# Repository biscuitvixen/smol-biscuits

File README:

# 🍪 Smol Biscuits SlimeVR Trackers

> **Tiny, lightweight, and long-lasting SlimeVR trackers for full-body tracking**

These are a derivative of SlimeVR trackers, designed to be **smaller**, **lighter**, and **longer lasting**! Perfect for comfortable all-day body tracking.

## ✨ Features

- 🔧 **Custom PCB** - Minimal footprint carrier board
- 🏠 **Custom 3D printed case** - Flexible two-piece design
- 💾 **Custom firmware** - Optimized derivative of SlimeVR firmware
- 🔋 **Extended battery life** - Efficient power management
- 📡 **Wireless connectivity** - nRF52840-based communication

## 📋 Table of Contents

- [🔧 Hardware](#-hardware)
  - [PCB Design](#pcb-design)
  - [Sensors](#sensors)
  - [Battery](#battery)
- [🏠 3D Printed Case](#-3d-printed-case)
- [💾 Firmware](#-firmware)
- [🔨 Assembly](#-assembly)
- [📡 Setup & Calibration](#-setup--calibration)

## 🔧 Hardware

### PCB Design

The PCB is designed in **KiCad** and the files can be found in the [`pcb`](./pcb) folder. The PCB is designed to be as small as possible, acting as a carrier board for a **Seeed Studio XIAO nRF52840** on the opposite side of the sensors.

### 📊 Sensors

| Component | Model | Function |
|-----------|-------|----------|
| **IMU** | ICM-45686 | 6-axis motion sensing |
| **Magnetometer** | QMC-6309 | Magnetic field detection |

#### 🎯 IMU: ICM-45686
High-performance 6-axis motion sensor providing accurate accelerometer and gyroscope data.

#### 🧭 Magnetometer: QMC-6309
Precision 3-axis magnetic sensor for improved orientation tracking.

### 🔋 Battery

The board requires a **LiPo battery**. Size based on your needs, but the included case is designed to fit a **150mAh battery** for optimal balance between size and runtime.

## 🏠 3D Printed Case

The case features an innovative **two-piece design** with a **flexible interlink**. The battery compartment and PCB housing are separate, connected by a flexible joint that allows the tracker to bend naturally around your body.

### 🔗 Design Features

- **Flexible interlink** - Allows bending around body contours
- **Strain relief** - Protects battery cable from damage  
- **Modular design** - Separate battery and PCB compartments

### 🎨 Print Materials

| Component | Recommended Material | Reason |
|-----------|---------------------|---------|
| **Flexi-link** | TPU | Flexibility and durability |
| **Base plates** | PETG | Strength under strain |
| **Top cover** | PLA or PETG | Aesthetic preference |
| **Switch** | PLA or PETG | Aesthetic preference |

> ⚠️ **Important**: The strap piece is under significant strain - avoid PLA for base plates as it may break!

## 💾 Firmware

### 🚀 Pre-Compiled Firmware

The firmware is included as a git submodule in the [`firmware`](./firmware) folder. It's a **fork of the SlimeVR firmware** with specific support for the Smol Biscuits PCB.

📦 **Quick Start**: Use the pre-compiled firmware files from the [releases section](../../releases) to program your trackers and receiver.

### 🛠️ Compiling Firmware Yourself

Want to customize or build from source? Follow these steps:

1. **Clone with submodules**:
   ```bash
   git clone --recurse-submodules https://github.com/biscuitvixen/smol-biscuits.git
   ```

2. **Follow SlimeVR dev documentation**:
   📖 [SlimeVR Compilation Guide](https://docs.slimevr.dev/smol-slimes/firmware/smol-compiling-firmware.html)

3. **Build with correct board target**:
   ```bash
   west build -p auto -b xiao_ble -d build . -- -DNCS_TOOLCHAIN_VERSION=NONE -DBOARD_ROOT=.
   ```

## 🔨 Assembly

### 🔧 Soldering the PCB

> ⚠️ **Safety First**: Use proper ventilation and ESD protection when soldering

#### Step-by-step Process:

1. **Solder sensor components** 📊
   - Solder the sensor components onto the PCB
   - ⚠️ Leave the XIAO nRF52840 for later

2. **Prepare battery terminals** 🔋
   - Pre-tin the battery terminals on the XIAO
   - Pre-tin the corresponding footprint on the PCB

3. **Position the XIAO** 📱
   - Use the solder jig to place the XIAO nRF52840
   - **Battery terminals facing up** ⬆️

4. **Apply flux and align** ✨
   - Apply flux to all connections
   - Place sensor PCB on top, aligning battery terminals

5. **Heat and bond** 🔥
   - Use square heat pass-through pads to melt solder
   - Apply gentle pressure to flatten boards together
   - Allow to cool completely ❄️

6. **Inspect and test** 🔍
   - Visual inspection of all joints
   - **Use multimeter to check for shorts** ⚡

7. **Complete connections** 🔗
   - Solder all castellated pins around PCB edge
   - Solder battery to back of sensor board

### 💾 Programming the PCB

#### Tracker Programming:

1. **Connect** 🔌 - USB-C cable to computer
2. **Bootloader mode** 🔄 - Double-tap reset button  
3. **Flash bootloader** 📥 - Copy `update-slimenrf_xiao_sense_bootloader-0.9.2-SlimeVR.7_nosd.uf2`
4. **Verify** ✅ - Should show as `SLIMENRF_XIAO_SENSE` drive
5. **Flash firmware** 🎯 - Copy `firmware_tracker.uf2` to drive
6. **Reboot** 🔄 - Device will restart with new firmware

#### 📡 Programming the Receiver

**For Holyiot receiver**:
- Use Nordic nRF Connect Programmer
- Flash `firmware_receiver.hex` file
- Follow [SlimeVR receiver documentation](https://docs.slimevr.dev) for other receivers

### 🏠 Assembling the Case

#### Step-by-step Assembly:

1. **Strap preparation** 📏
   - Slide bases onto 30mm strap
   - **Ensure notches face each other** 🔄

2. **Flex link installation** 🔗
   - Place flex link between bases in designated slot

3. **Battery compartment** 🔋
   - Insert battery spacer between strap and battery
   - Position battery on top of spacer

4. **Secure battery** 🔒
   - Hold battery in place by wires
   - Snap battery base into place

5. **PCB installation** 📱
   - Place PCB into PCB base
   - **Align switch with cutout** ⚙️

6. **Switch mechanism** 🎛️
   - Slide switch slider over PCB switch

7. **Final assembly** ✅
   - Ensure case slides correctly over switch
   - Snap top cover into place

8. **Strap adjustment** 📐
   - Adjust strap to fit comfortably
   - Secure in place

## 📡 Setup & Calibration

For complete setup and calibration instructions, refer to the official SlimeVR documentation:

🔗 **[SlimeVR Pairing & Calibration Guide](https://docs.slimevr.dev/smol-slimes/firmware/smol-pairing-and-calibration.html)**

---

## 🎊 Congratulations!

**Your Smol Biscuits SlimeVR trackers are ready to use!**

Enjoy your new lightweight, comfortable full-body tracking experience! �✨

---

## 📄 License

### 🔧 Hardware Designs
**PCB files, 3D models, schematics, and case designs** are licensed under:
- **CC BY-NC-SA 4.0** - [Full License Text](LICENSE-CC-BY-NC-SA)

**Personal and educational use**: ✅ Free to use, modify, and share  
**Commercial use**: ❌ Requires separate license - contact [onlybiscuit7@gmail.com]

### 💾 Firmware
**Firmware** retains the original SlimeVR license terms:
- Original SlimeVR licenses: [MIT](LICENSE-MIT) | [Apache 2.0](LICENSE-APACHE)
- See firmware submodule for complete licensing information

### 🤝 What This Means
- **Hobbyists & Makers**: Build away! Just credit me and share improvements
- **Companies**: Want to sell these? Let's talk revenue sharing or licensing
- **Everyone**: Improvements must be shared under the same terms

### 🤝 Third-Party Components
- **SlimeVR Firmware**: Check firmware submodule for licensing terms
- **Dependencies**: Various open source licenses (see individual components)

## 🤝 Contributing

I welcome contributions! Please feel free to submit pull requests or open issues.

## 📞 Support

For support and questions:
- 📖 Check the [SlimeVR Documentation](https://docs.slimevr.dev)
- 💬 Join the SlimeVR Discord community
- 🐛 Report issues on GitHub

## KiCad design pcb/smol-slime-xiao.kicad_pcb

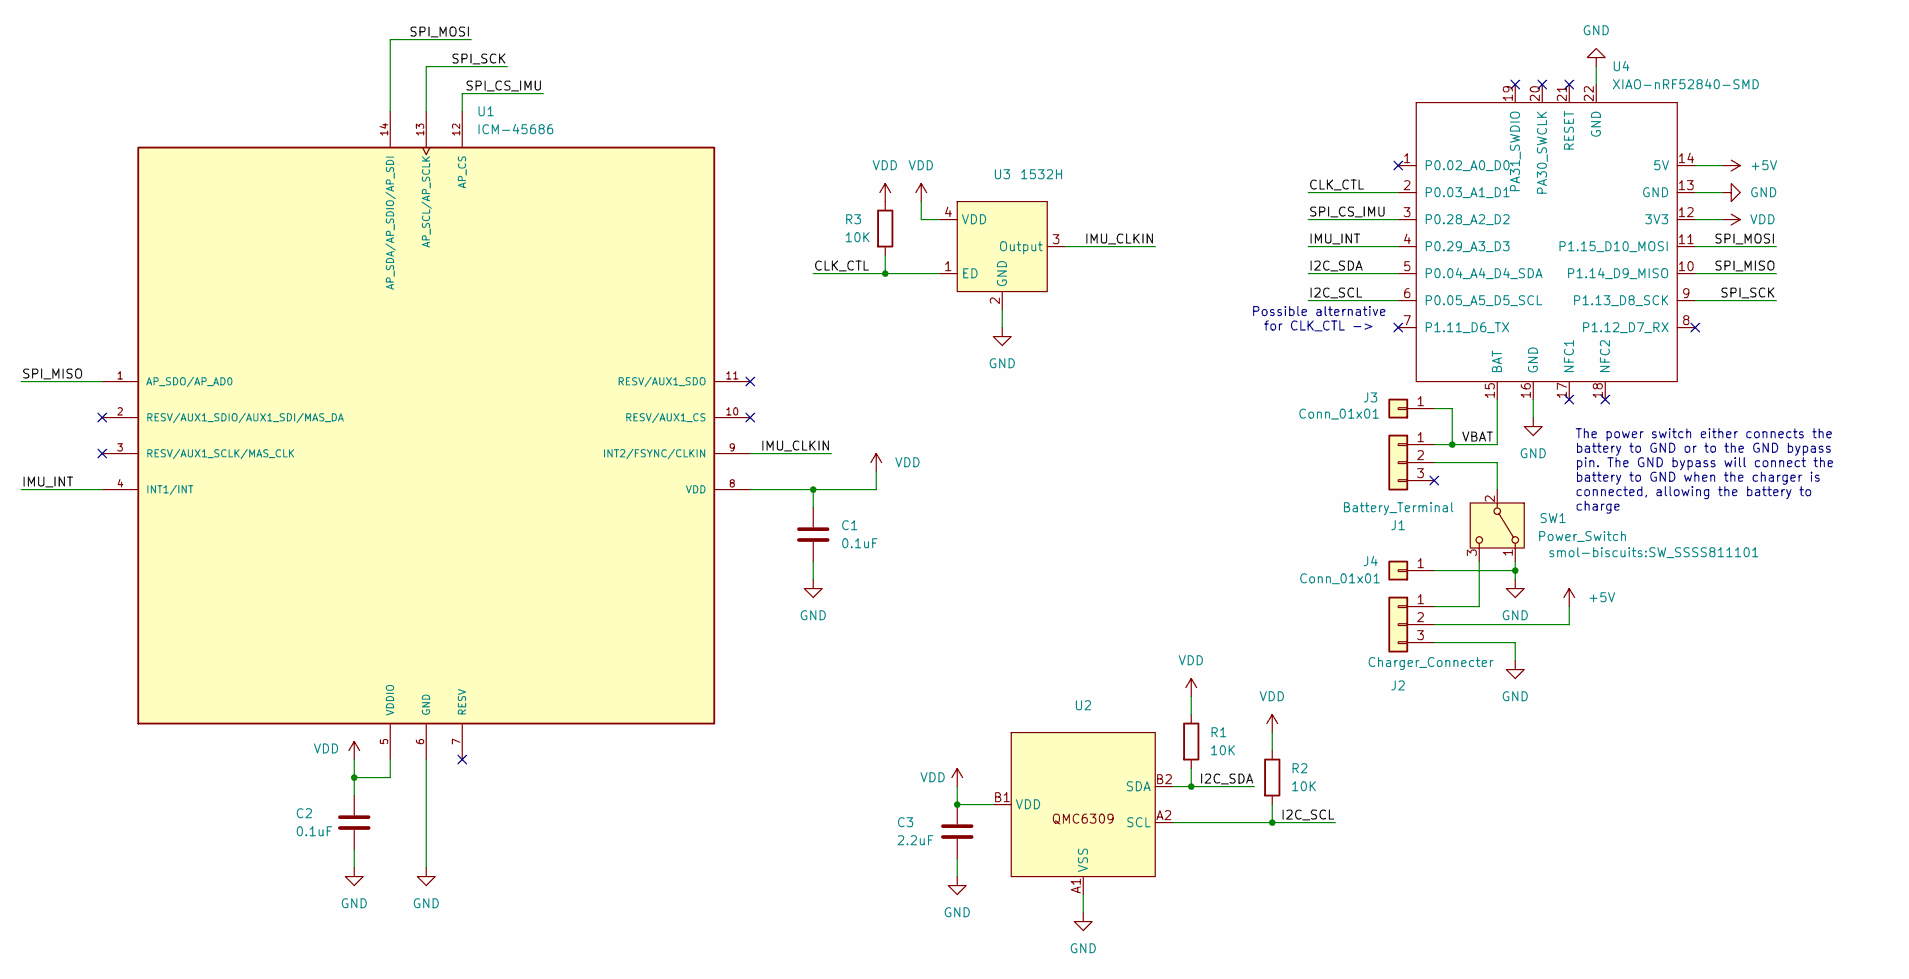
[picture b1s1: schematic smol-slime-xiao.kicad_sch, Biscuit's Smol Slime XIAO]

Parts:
C1, C2: 0.1uF; C_0603_1608Metric; LCSC PN C1591
C3: 2.2uF; C_0603_1608Metric; LCSC PN C100082
J1: Battery_Terminal; JST_PH2_SMT; LCSC PN C295747
J2: Charger_Connecter; PinPads_1x03_P2.54mm
J3, J4: Conn_01x01; Heat_Pad_1.0x1.0mm
R1, R2, R3: 10K; R_0603_1608Metric; LCSC PN C15401
SW1: Power_Switch; SW_SSSS811101; LCSC PN C109335
U1: ICM-45686; IC_ICM-45686; PARTREV 0.2; LCSC PN C22459454
U2: QMC6309; LCSC PN C5439871
U3: 1532H; Crystal_SMD_3225-4Pin_3.2x2.5mm_Silkscreenfix; LCSC PN C252344
U4: XIAO-nRF52840-SMD; XIAO-nRF52840-SMD-FixedSilkscreen

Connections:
+5V: J2.2, U4.14 (5V)
/CLK_CTL: R3.2, U3.1 (ED), U4.2 (P0.03_A1_D1)
/I2C_SCL: R2.2, U2.A2 (SCL), U4.6 (P0.05_A5_D5_SCL)
/I2C_SDA: R1.2, U2.B2 (SDA), U4.5 (P0.04_A4_D4_SDA)
/IMU_CLKIN: U1.9 (INT2/FSYNC/CLKIN), U3.3 (Output)
/IMU_INT: U1.4 (INT1/INT), U4.4 (P0.29_A3_D3)
/SPI_CS_IMU: U1.12 (AP_CS), U4.3 (P0.28_A2_D2)
/SPI_MISO: U1.1 (AP_SDO/AP_AD0), U4.10 (P1.14_D9_MISO)
/SPI_MOSI: U1.14 (AP_SDA/AP_SDIO/AP_SDI), U4.11 (P1.15_D10_MOSI)
/SPI_SCK: U1.13 (AP_SCL/AP_SCLK), U4.9 (P1.13_D8_SCK)
/VBAT: J1.1, J3.1 (Pin_1_1), U4.15 (BAT)
GND: C1.1, C2.1, C3.1, J2.3, J4.1 (Pin_1_1), SW1.1 (A), U1.6 (GND), U2.A1 (VSS), U3.2 (GND), U4.13 (GND), U4.16 (GND), U4.22 (GND)
unnamed: J1.2, SW1.2 (B)
unnamed: J2.1, SW1.3 (C)
VDD: C1.2, C2.2, C3.2, R1.1, R2.1, R3.1, U1.5 (VDDIO), U1.8 (VDD), U2.B1 (VDD), U3.4 (VDD), U4.12 (3V3)

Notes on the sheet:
The power switch either connects the battery to GND or to the GND bypass pin. The GND bypass will connect the battery to GND when the charger is connected, allowing the battery to charge
Possible alternative for CLK_CTL ->

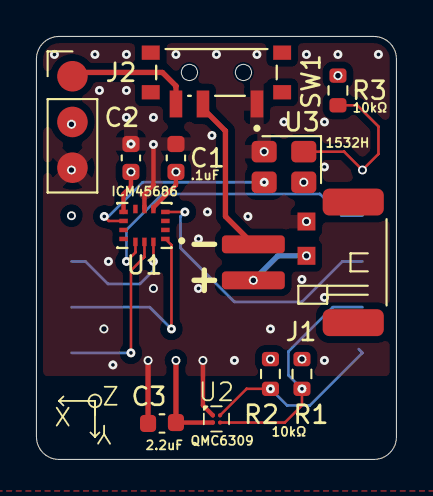
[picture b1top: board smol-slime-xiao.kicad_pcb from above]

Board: 4 copper layers, 20.0 x 23.5 mm, 17 parts (1 on the bottom side), 15 nets.

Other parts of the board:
LogoCalligraphy: LOGO
LogoHead: LOGO

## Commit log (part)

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2025-06-16 Add ignore
2025-06-17 Create empty project base
2025-06-17 Ignore zip directory
2025-06-18 Include main IC documentation
2025-06-18 Import ICM_45686 symbol
2025-06-18 Ignore kicad backups
2025-06-18 Convert footprint for KiCad 9 and add library
2025-06-18 Add 3d model for ICM_45656
2025-06-19 Add QMC6309 symbol and footprint
2025-06-19 Add schematic symbol for crystal
2025-06-20 Add 1532H4 oscillator
2025-06-20 Add capacitors
2025-06-21 Update design
2025-06-23 Added GND and VDD reference for Magnetometer
2025-07-02 Add Seeed OPL KiCad library as submodule
2025-07-02 Import XIAO footprint library
2025-07-02 Import XIAO symbol library
2025-07-03 Add XIAO MCU symbol
2025-07-03 Add IMU net labels
2025-07-03 Add .lck to .gitignore and remove .lck files from tracking
2025-07-03 Add net labels for QMC6309
2025-07-03 Added net labels to 1532H Oscillator
2025-07-03 Neaten QMC6309 wiring
2025-07-03 Neaten IMU wiring
2025-07-03 Add SPI connections to MCU
2025-07-03 Add I2C connections to MCU
2025-07-03 Add oscillator connections to MCU
2025-07-03 Fix label formatting
2025-07-03 Add pin assignments for MCU
2025-07-03 Add pull-up to ED for oscillator
2025-07-03 Rearrange for neatness
2025-07-03 Update components
2025-07-04 Roughly lay out components
2025-07-04 Re-arrange for optimal magnetometer placement
2025-07-04 Add MCU connectors
2025-07-04 Fix edge cuts
2025-07-04 Rework board shape and arrangement
2025-07-16 Add JLCPCB design rules for board validation
2025-07-16 Homogenise connector terminals
2025-07-16 Create 2.54mm pad footprint
2025-07-16 Add pad to power connector
2025-07-16 Update edge-cuts for board
2025-07-17 Added power pads to board
2025-07-17 Add battery JST connector
2025-07-17 Add descriptions to silkscreen
2025-07-17 Update pin pad footprint
2025-07-17 Revert silkscreen verbosity
2025-07-18 Changed JST to SMT
2025-07-18 Add pours
2025-07-18 Add descriptors
2025-07-18 Move CLK_CTL to alternate GPIO
2025-07-18 Fix XIAO silkscreen overlap
2025-07-18 Fix default pad clearance on QMC6309 footprint
2025-07-18 Connect QMC
2025-07-18 Fix keep out zone
2025-07-18 Fix QMC silkscreen clearance
2025-07-18 Add JST vias
2025-07-18 Fix C2 GND connection
2025-07-22 PCB Current
2025-07-22 Add power switch
2025-07-23 Create VBAT_GND net for charge connector bypass
2025-07-23 Create 3 pad connector
2025-07-23 Changed charge connector footprint to 3 pin variant
2025-07-25 Update switch symbol and circuit logic to avail parts
2025-07-29 Reorganise PCB
2025-07-29 Tied ground vias
2025-07-29 Balance VDD plane GND via cutoffs
2025-07-29 Fix DRC errors
2025-08-03 Add part numbers and datasheets for BOM
2025-08-03 Fix mis-wired oscillator
2025-08-03 Add logo, details and dedication
2025-08-03 Fix footprint mismatch
2025-08-03 Correct part number field name
2025-08-03 Generate fabrication gerbers and drill files
2025-08-03 Generate BOM and Placement and move gerbers into production dir
2025-08-03 Update oscillator part
2025-08-03 Update fro production
2025-08-24 Add modified firmware repo forks as submodules
2025-08-25 Update attribution
2025-08-25 Fix missing reference designators
2025-08-25 Update fabrication files for release
2025-08-25 Fix fab path
2025-09-18 Add schematic pdf
2025-10-26 Add README file for Smol Biscuits SlimeVR Trackers
2025-10-27 Update README with firmware compilation and assembly instructions
2025-10-27 Add LICENSE files for firmware and hardware designs
2025-10-27 Revise README to enhance clarity and detail on features, assembly, and licensing for Smol Biscuits SlimeVR Trackers
2025-10-27 Add licensing files for firmware and hardware, update README with license details
2025-10-27 Rename readme for parsing
2025-12-23 Expand board edges
2025-12-23 Roughly re-arrange parts
2025-12-27 Refine component placement
